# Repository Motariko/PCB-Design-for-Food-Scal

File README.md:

# PCB-Design-for-Food-Scal: Custom PCB Design for Digital Food Scale

This repository contains the custom Printed Circuit Board (PCB) design for the ScalPro smart food scale project. The hardware is engineered to support precise weight measurement, user interaction via physical controls, and an integrated display system.

## Hardware Architecture and Schematic Design

The PCB design is centered around the ESP32 microcontroller, utilizing a dual-row header configuration for modularity and ease of maintenance. The circuit integrates several specialized subsystems to ensure reliable operation in a kitchen environment.

The Signal Acquisition Interface features a dedicated header for the HX711 Load Cell Amplifier, which is essential for high-resolution weight data acquisition with minimal signal interference. User input management is handled by multiple hot-swap tactile switches designed for primary functions such as Tare, Data Transmission, and System Sleep, providing a robust physical interface. Additionally, a standardized I2C LCD connector includes integrated voltage jumper points to allow for flexible power rail configuration across various display modules. The power distribution network is designed with dedicated input headers and battery management terminals to support portable operation via rechargeable battery cells.

## PCB Layout and Routing Specifications

The PCB was developed with a strict focus on signal integrity and power stability. The layout utilizes a single-layer routing strategy with widened power traces to minimize voltage drop and ensure consistent performance during high-current wireless transmissions, such as WiFi or Bluetooth operations.

Thermal and ground management is achieved through a large ground pour, which provides necessary electromagnetic interference shielding and effective heat dissipation for the onboard voltage regulators and the ESP32 module. The component placement is highly optimized to maintain a compact form factor, making it suitable for integration into a professional kitchen scale enclosure.

## Technical Summary

The main controller for this design is an ESP32 development board mounted via headers for serviceability. The board provides full hardware support for HX711 sensors, I2C liquid crystal displays, and Serial UART communication for debugging purposes. It supports dual-mode power input through either an external voltage source or an integrated battery system.

Developed by Aitsara Phetsila, Computer Engineering Student at Ramkhamhaeng University.

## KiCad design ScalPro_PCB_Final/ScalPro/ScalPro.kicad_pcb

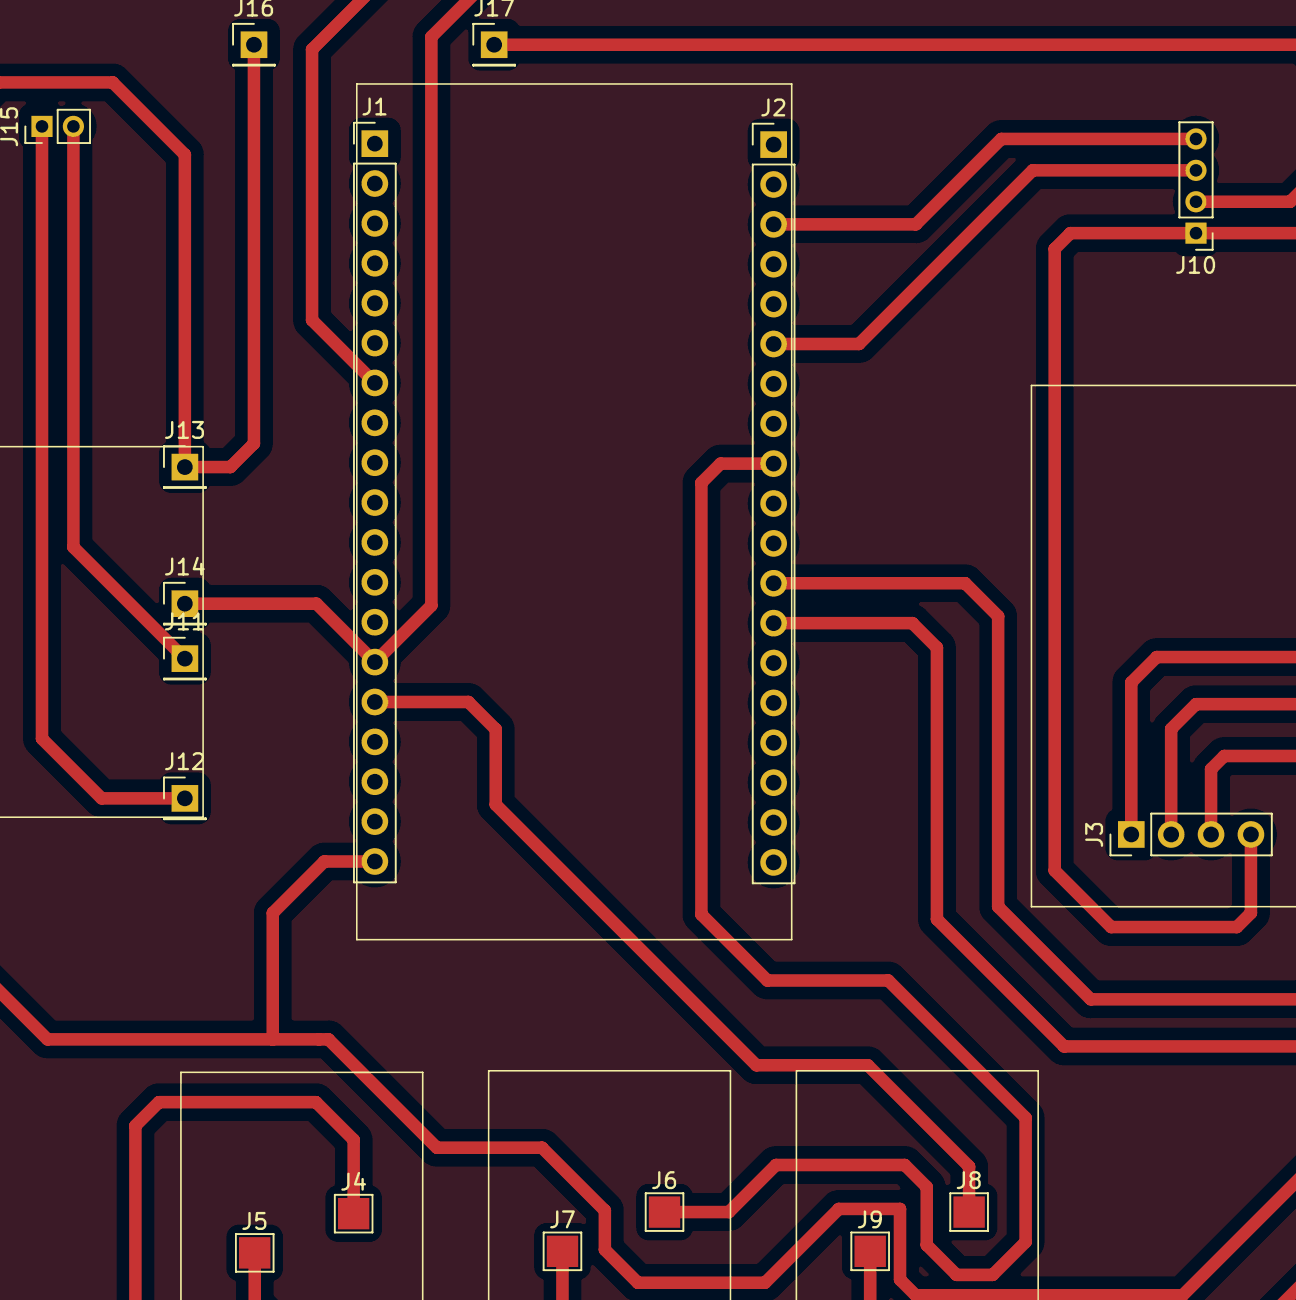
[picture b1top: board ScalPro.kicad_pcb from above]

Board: 2 copper layers, 17 parts (0 on the bottom side), 12 nets.

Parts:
J1: ESP32_L; PinHeader_1x19_P2.54mm_Vertical
J2: ESP32_R; PinHeader_1x19_P2.54mm_Vertical
J3: HX711_PIN; PinHeader_1x04_P2.54mm_Vertical
J4: HOTSWAPup1; TestPoint_Pad_2.0x2.0mm
J5: HOTSWAPdown1; TestPoint_Pad_2.0x2.0mm
J6: HOTSWAPup2; TestPoint_Pad_2.0x2.0mm
J7: HOTSWAPdown2; TestPoint_Pad_2.0x2.0mm
J8: HOTSWAPup3; TestPoint_Pad_2.0x2.0mm
J9: HOTSWAPdown3; TestPoint_Pad_2.0x2.0mm
J10: LCDPIN; PinHeader_1x04_P2.00mm_Vertical
J11: B-; PinHeader_1x01_P2.54mm_Vertical
J12: B+; PinHeader_1x01_P2.54mm_Vertical
J13: VCC; PinHeader_1x01_P2.54mm_Vertical
J14: GND; PinHeader_1x01_P2.54mm_Vertical
J15: Vin; PinHeader_1x02_P2.00mm_Vertical
J16: Jampper_VCC_to_LCD; PinHeader_1x01_P2.54mm_Vertical
J17: Jampper_LCD_to_VCC; PinHeader_1x01_P2.54mm_Vertical

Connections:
unnamed: J1.7, J4.1
unnamed: J1.14, J3.4, J5.1, J7.1, J9.1, J10.1, J14.1
unnamed: J1.15, J8.1
unnamed: J1.19, J3.1, J13.1, J16.1
unnamed: J2.9, J6.1
unnamed: J2.12, J3.3
unnamed: J2.13, J3.2
unnamed: J10.2, J17.1
unnamed: J2.6, J10.3
unnamed: J2.3, J10.4
unnamed: J11.1, J15.2
unnamed: J12.1, J15.1
